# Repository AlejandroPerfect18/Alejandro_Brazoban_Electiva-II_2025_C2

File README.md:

Alejandro_Brazoban_Electiva-II_2025_C2

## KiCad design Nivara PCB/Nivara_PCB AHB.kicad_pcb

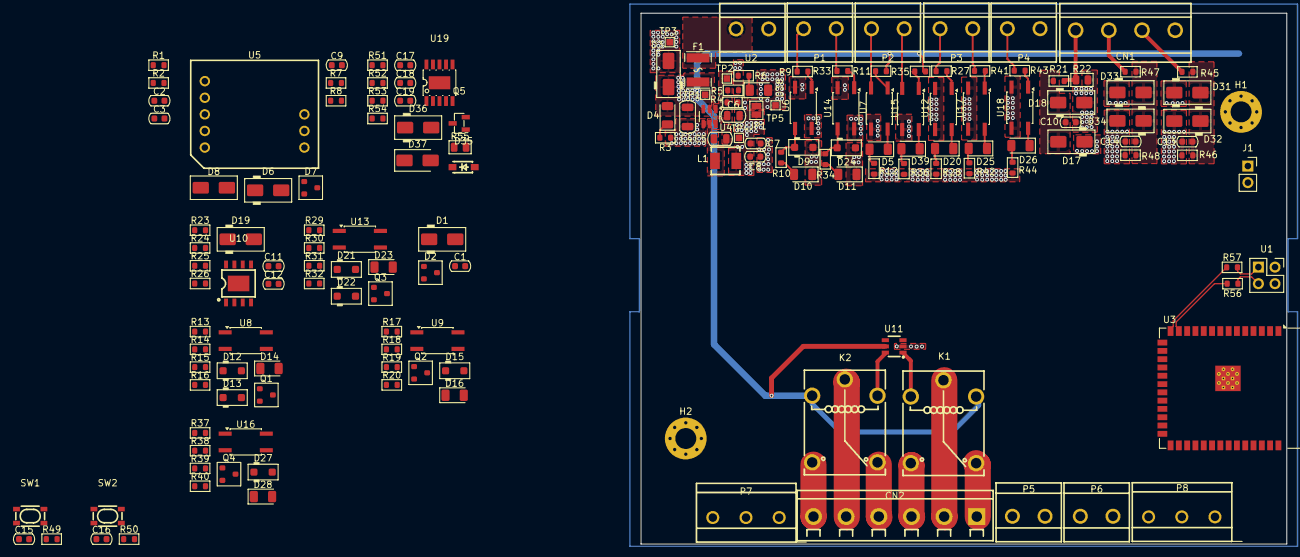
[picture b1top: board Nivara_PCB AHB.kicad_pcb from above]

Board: 4 copper layers, 162 parts (0 on the bottom side), 108 nets.

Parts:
C1, C3, C13, C14: 100nF; C_0603_1608Metric
C2, C7, C8: 22uF; C_0603_1608Metric
C4: 10uF; C_1206_3216Metric
C5: 100nF; C_0805_2012Metric
C6: 100pF; C_0805_2012Metric
C9: 10uF; C_0603_1608Metric
C10: 10nF; C_0603_1608Metric
C11, C19: 0.1uF; C_0603_1608Metric
C12, C15, C16, C18: 1uF; C_0603_1608Metric
C17: 220pF; C_0603_1608Metric
CN1: ANALOG_IN; CONN-TH_DB128V-5.0-4P
CN2: RELAY; CONN-TH_DB126V-5.0-6P-GN
D1: SS12; D_SMA
D2, D7: SM712; SOT-23
D3, D36: SMAJ33A; D_SMA
D4, D5, D10, D11, D14, D16, D20, D23, D25, D26, D28, D38, D39: IR26-21C_L110_TR8; LED_1206_3216Metric
D6, D17, D18, D31, D32, D33, D34: SMAJ5.0A; D_SMA
D8: SMAJ12CA; D_SMA_TVS
D9, D12, D13, D15, D21, D22, D24, D27: PMEG4010CEH; D_SOD-123F
D19: SMAJ12A; D_SMA
D35: BZT52C12_C2891780; SOD-123_L2.7-W1.6-LS3.7-RD-1
D37: MRA4007T3G; D_SMA
F1: BSMD1812-150-33V; F1812
H1, H2: MountingHole_Pad; MountingHole_3.2mm_M3_Pad_Via
J1: AUXILIAR; PinSocket_1x02_P2.54mm_Vertical
JP1: SolderJumper_2_Open; SolderJumper-2_P1.3mm_Open_Pad1.0x1.5mm
K1, K2: SRA-24VDC-CL; RELAY-TH_SRA-X-CX
L1: CXP0420-6R8M-AG(6.8UH); IND-SMD_L4.4-W4.2_CXP0420
P1: NPN_IN; CONN-TH_XY126V-5.0-2P
P2: PNP_IN; CONN-TH_XY126V-5.0-2P
P3: D_IN; CONN-TH_XY126V-5.0-2P
P4: RUN/STOP; CONN-TH_XY126V-5.0-2P
P5: NPN_OUT; CONN-TH_XY126V-5.0-2P
P6: PNP_OUT; CONN-TH_XY126V-5.0-2P
P7: RS485; CONN-TH_3P-P5.00_WJ500V-5.08-3P
P8: ANALOG_OUT.; CONN-TH_3P-P5.00_WJ500V-5.08-3P
Q1, Q3: IRLML0040; SOT-23
Q2, Q4: AO3407A; SOT-23
Q5: IRLML6402TRPBF-JSM; SOT-23-3_L2.9-W1.3-P1.90-LS2.4-BR
R1, R2, R56, R57: 33; R_0603_1608Metric
R3: 1k2; R_0603_1608Metric
R4: 196k; R_0603_1608Metric
R5: 62k; R_0603_1608Metric
R6, R13, R17, R18, R29, R37, R38: 100; R_0603_1608Metric
R7, R8: R_0603; R_0603_1608Metric
R9, R11, R21, R27, R33, R35, R41, R43: 1k; R_0603_1608Metric
R10, R12, R28, R34, R36, R42, R44: 140; R_0603_1608Metric
R14, R30: 22k; R_0603_1608Metric
R15, R31: 20k; R_0603_1608Metric
R16, R20, R32, R40: 1.5k; R_0603_1608Metric
R19, R39, R45, R54: 100k; R_0603_1608Metric
R22: 145; R_0805_2012Metric
R23, R24, R51, R52: 4K7; R_0603_1608Metric
R25: 0; R_0603_1608Metric
R26: 10K; R_0603_1608Metric
R46, R48, R49, R50: 10k; R_0603_1608Metric
R47: 24k; R_0603_1608Metric
R53: 2.5k; R_0603_1608Metric
R55: 15; R_0805_2012Metric
SW1, SW2: SKRPACE010; KEY-SMD_4P-L4.2-W3.2-P2.20-LS4.6
TP1: +VCC1; TestPoint_Pad_1.0x1.0mm
TP2: FB; TestPoint_Pad_1.0x1.0mm
TP3: GND; TestPoint_Pad_1.0x1.0mm
TP4: +3.3V; TestPoint_Pad_1.0x1.0mm
TP5: +3.3Vout; TestPoint_Pad_1.0x1.0mm
U1: 2.54-2*2; PinSocket_2x02_P2.54mm_Vertical
U2: FUENTE IN; CONN-TH_XY126V-5.0-2P
U3: ESP32-S3-WROOM-1
U4: AP63200WU; TSOT-23-6
U5: RSM3485ECHT_C2992406; COMM-TH_8P-L19.5-W16.5-P2.54-BL
U6, U7, U8, U9, U12, U13, U14, U15, U16, U17, U18: LTV-357T; SO-4_4.4x3.6mm_P2.54mm
U10: GP8201S-TC50-EW; ESOP-8_L4.9-W3.9-P1.27-LS6.0-BL-EP
U11: LK1802; SOT-23-6_L2.9-W1.6-P0.95-LS2.8-BR
U19: GP8303-TC50-EW; ESOP-10_L4.9-W3.9-P1.00-LS6.1-BL-EP

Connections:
+3.3V: C2.1, C3.1, C9.1, C15.2, C16.2, D6.1 (K), D17.1 (K), D31.1 (K), D33.1 (K), D38.2 (A), JP1.2 (B), R12.1, R17.1, R23.1, R24.1, R26.1, R28.1, R36.1, R37.1, R42.1, R44.1, R49.1, R50.1, R51.1, R52.1, TP5.1, U3.2 (3V3), U5.1 (VCC), U6.4, U14.4
/D+: D2.1 (A1), R56.1, U1.4
/D-: D2.2 (A2), R57.1, U1.2
/NIVARA_BOARD/4-20mA_IN/ESP_4-20_IN: C10.1, D17.2 (A), D18.1 (K), R21.1, U3.4 (GPIO4/TOUCH4/ADC1_CH3)
/NIVARA_BOARD/A0_10_IN_1: CN1.2, R47.2
/NIVARA_BOARD/A0_32_IN_1: CN1.3, R45.2
/NIVARA_BOARD/A0_V_OUT_1: C11.1, D19.1 (K), P8.1, U10.6 (VOUT)
/NIVARA_BOARD/A4_20_IN_1: CN1.1, R21.2, R22.1
/NIVARA_BOARD/AUX_1: J1.1, R1.2
/NIVARA_BOARD/AUX_2: J1.2, R2.2
/NIVARA_BOARD/A_0-10_IN/A_V_OUT: C14.1, D33.2 (A), D34.1 (K), R47.1, R48.2, U3.6 (GPIO6/TOUCH6/ADC1_CH5)
/NIVARA_BOARD/A_0-32_IN/A_V_OUT: C13.1, D31.2 (A), D32.1 (K), R45.1, R46.2, U3.5 (GPIO5/TOUCH5/ADC1_CH4)
/NIVARA_BOARD/A_I_OUT/SCLK_C: R52.2, U3.21 (GPIO13/TOUCH13/ADC2_CH2/FSPIQ/FSPIIO7/S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), U19.1 (SLCK)
/NIVARA_BOARD/A_I_OUT/SDA_C: R51.2, U3.22 (GPIO14/TOUCH14/ADC2_CH3/FSPIWP/FSPIDQS/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), U19.2 (SDA)
/NIVARA_BOARD/A_V_OUT/ESP_SEL_VOUT: C12.1, R25.2, R26.2, U3.18 (GPIO10/TOUCH10/ADC1_CH9/FSPICS0/FSPIIO4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)
/NIVARA_BOARD/A_V_OUT/SCLK_V: R24.2, U3.19 (GPIO11/TOUCH11/ADC2_CH0/FSPID/FSPIIO5/S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), U10.1 (SCLK)
/NIVARA_BOARD/A_V_OUT/SDA_V: R23.2, U3.20 (GPIO12/TOUCH12/ADC2_CH1/FSPICLK/FSPIIO6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), U10.2 (SDA)
/NIVARA_BOARD/BUTTON1/BUTTON_PIN: R50.2, SW2.3, U3.3 (EN)
/NIVARA_BOARD/BUTTON/BUTTON_PIN: R49.2, SW1.3, U3.27 (GPIO0/BOOT)
/NIVARA_BOARD/DRIVER_RS485/UART_IN: U3.11 (GPIO18/U1RXD/ADC2_CH7/CLK_OUT3), U5.4 (RXD)
/NIVARA_BOARD/DRIVER_RS485/UART_OUT: U3.10 (GPIO17/U1TXD/ADC2_CH6), U5.3 (TXD)
/NIVARA_BOARD/D_IN_1: P3.1, R27.1
/NIVARA_BOARD/D_IN_1/D_OUT: D20.1 (K), U3.28 (SPIIO6/GPIO35/FSPID/SUBSPID), U12.4
/NIVARA_BOARD/D_IN_2: P3.2, R41.1
/NIVARA_BOARD/D_IN_2/D_OUT: D25.1 (K), U3.29 (SPIIO7/GPIO36/FSPICLK/SUBSPICLK), U17.4
/NIVARA_BOARD/I_OUT: D37.1 (K), P8.2
/NIVARA_BOARD/NPN_IN_1: P1.1, R9.1
/NIVARA_BOARD/NPN_IN_1/NPN_OUT: D9.1 (K), R10.1, U3.32 (MTCK/GPIO39/CLK_OUT3/SUBSPICS1), U6.3
/NIVARA_BOARD/NPN_IN_2: P1.2, R33.1
/NIVARA_BOARD/NPN_IN_2/NPN_OUT: D24.1 (K), R34.1, U3.33 (MTDO/GPIO40/CLK_OUT2), U14.3
/NIVARA_BOARD/NPN_OUT_1: P5.1, R13.1
/NIVARA_BOARD/NPN_OUT_1/NPN_OUT: D13.2 (A), D14.1 (K), Q1.3 (D), U3.34 (MTDI/GPIO41/CLK_OUT1)
/NIVARA_BOARD/NPN_OUT_2: P5.2, R29.1
/NIVARA_BOARD/NPN_OUT_2/NPN_OUT: D22.2 (A), D23.1 (K), Q3.3 (D), U3.35 (MTMS/GPIO42)
/NIVARA_BOARD/PNP_IN_1: P2.1, U7.2
/NIVARA_BOARD/PNP_IN_1/PNP_OUT: D5.1 (K), U3.8 (GPIO15/U0RTS/ADC2_CH4/XTAL_32K_P), U7.4
/NIVARA_BOARD/PNP_IN_2: P2.2, U15.2
/NIVARA_BOARD/PNP_IN_2/PNP_OUT: D39.1 (K), U3.9 (GPIO16/U0CTS/ADC2_CH5/XTAL_32K_N), U15.4
/NIVARA_BOARD/PNP_OUT_1: D15.1 (K), P6.1, Q2.3 (D), R20.1
/NIVARA_BOARD/PNP_OUT_1/PNP_IN: U3.23 (GPIO21), U9.2
/NIVARA_BOARD/PNP_OUT_2: D27.1 (K), P6.2, Q4.3 (D), R40.1
/NIVARA_BOARD/PNP_OUT_2/PNP_IN: U3.24 (GPIO47/SPICLK_P/SUBSPICLK_P_DIFF), U16.2
/NIVARA_BOARD/PowerSupply/BST: C5.1, U4.6 (BST)
/NIVARA_BOARD/PowerSupply/FB: C6.1, R4.2, R5.1, TP2.1, U4.1 (FB)
/NIVARA_BOARD/PowerSupply/SW: C5.2, L1.1, U4.5 (SW)
/NIVARA_BOARD/PowerSupply/VOUT: C6.2, C7.1, C8.1, JP1.1 (A), L1.2, R4.1, TP4.1
/NIVARA_BOARD/RELAY1&2/ESP_RLY2: U3.39 (GPIO1/TOUCH1/ADC1_CH0), U11.3 (1B)
/NIVARA_BOARD/RELAY1&2/ESP_RY1: U3.38 (GPIO2/TOUCH2/ADC1_CH1), U11.4 (2B)
/NIVARA_BOARD/RLY_1_C: CN2.2, K1.5
/NIVARA_BOARD/RLY_1_NC: CN2.1, K1.2
/NIVARA_BOARD/RLY_1_NO: CN2.3, K1.1
/NIVARA_BOARD/RLY_2_C: CN2.5, K2.5
/NIVARA_BOARD/RLY_2_NC: CN2.4, K2.2
/NIVARA_BOARD/RLY_2_NO: CN2.6, K2.1
/NIVARA_BOARD/RS485_A: P7.1, R7.2
/NIVARA_BOARD/RS485_B: P7.2, R8.2
/NIVARA_BOARD/RUN_STOP/D_OUT: D26.1 (K), U3.30 (SPIDQS/GPIO37/FSPIQ/SUBSPIQ), U18.4
/NIVARA_BOARD/RUN/STOP: P4.1, R43.1
/NIVARA_BOARD/USB_D+: R56.2, U3.13 (GPIO19/U1RTS/ADC2_CH8/CLK_OUT2/USB_D-)
/NIVARA_BOARD/USB_D-: R57.2, U3.14 (GPIO20/U1CTS/ADC2_CH9/CLK_OUT1/USB_D+)
/VIN: F1.1, U2.1
GND: C1.2, C2.2, C3.2, C4.2, C7.2, C8.2, C9.2, C10.2, C11.2, C12.2, C13.2, C14.2, C15.1, C16.1, C17.2, C18.2, C19.2, CN1.4, D2.3 (Com), D3.2 (A), D6.2 (A), D7.3 (Com), D9.2 (A), D10.1 (K), D11.1 (K), D12.2 (A), D15.2 (A), D16.1 (K), D18.2 (A), D19.2 (A), D21.2 (A), D24.2 (A), D27.2 (A), D28.1 (K), D32.2 (A), D34.2 (A), D36.2 (A), H1.1, H2.1, P4.2, P7.3, P8.3, Q1.2 (S), Q3.2 (S), R3.1, R5.2, R6.1, R14.2, R22.2, R30.2, R46.1, R48.1, R53.2, R54.2, SW1.2, SW2.2, TP3.1, U1.1, U2.2, U3.1 (GND), U3.40 (GND), U3.41 (GND), U4.4 (GND), U5.2 (GND), U5.5 (CON), U6.2, U7.3, U8.2, U9.3, U10.5 (GND), U11.2 (E), U12.2, U12.3, U13.2, U14.2, U15.3, U16.3, U17.2, U17.3, U18.2, U18.3, U19.6 (GND)
unnamed: D1.2 (A), U1.3
unnamed: D4.1 (K), R3.2
unnamed: D5.2 (A), R12.2
unnamed: D7.1 (A1), D8.2 (A), R7.1, U5.9 (A)
unnamed: D7.2 (A2), D8.1 (K), R8.1, U5.8 (B)
unnamed: D10.2 (A), R10.2
unnamed: D11.2 (A), R34.2
unnamed: D12.1 (K), Q1.1 (G), R14.1, U8.3
unnamed: D14.2 (A), R16.2
unnamed: D16.2 (A), R20.2
unnamed: D20.2 (A), R28.2
unnamed: D21.1 (K), Q3.1 (G), R30.1, U13.3
unnamed: D23.2 (A), R32.2
unnamed: D25.2 (A), R42.2
unnamed: D26.2 (A), R44.2
unnamed: D28.2 (A), R40.2
unnamed: C18.1, D35.2 (A), Q5.1 (G), R54.1
unnamed: C19.1, D36.1 (K), Q5.3 (D), R55.1
unnamed: D37.2 (A), R55.2
unnamed: D38.1 (K), R6.2
unnamed: D39.2 (A), R36.2
unnamed: Q2.1 (G), R18.1, R19.2
unnamed: Q4.1 (G), R38.1, R39.2
unnamed: Q5.2 (S), U19.8 (IOUT)
unnamed: R9.2, U6.1
unnamed: R11.2, U7.1
unnamed: R13.2, U8.1
unnamed: R15.2, U8.4
unnamed: R17.2, U9.1
unnamed: R18.2, U9.4
unnamed: R27.2, U12.1
unnamed: R29.2, U13.1
unnamed: R31.2, U13.4
unnamed: R33.2, U14.1
unnamed: R35.2, U15.1
unnamed: R37.2, U16.1
unnamed: R38.2, U16.4
unnamed: R41.2, U17.1
unnamed: R43.2, U18.1
unnamed: R2.1, U3.26 (GPIO45)
unnamed: R1.1, U3.25 (GPIO48/SPICLK_N/SUBSPICLK_N_DIFF)
unnamed: R25.1, U10.7 (SEL)
unnamed: K1.4, U11.1 (1C)
unnamed: K2.3, U11.6 (2C)
unnamed: C17.1, R53.1, U19.7 (SET)
VCC: C1.1, C4.1, D1.1 (K), D3.1 (K), D4.2 (A), D13.1 (K), D22.1 (K), D35.1 (K), F1.2, K1.3, K2.4, Q2.2 (S), Q4.2 (S), R11.1, R15.1, R16.1, R19.1, R31.1, R32.1, R35.1, R39.1, TP1.1, U4.2 (EN), U4.3 (IN), U10.4 (VCC), U11.5 (COM), U19.5 (VCC)

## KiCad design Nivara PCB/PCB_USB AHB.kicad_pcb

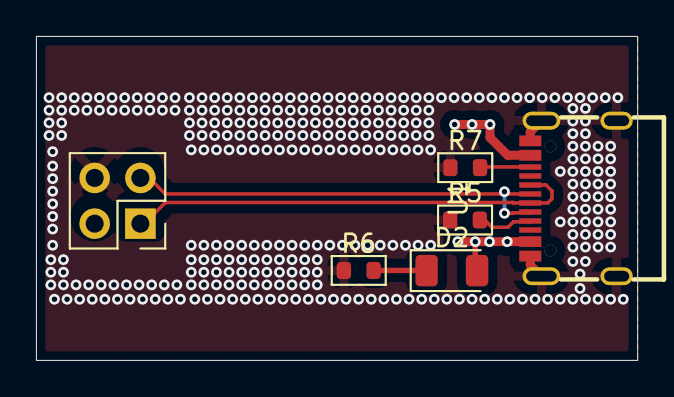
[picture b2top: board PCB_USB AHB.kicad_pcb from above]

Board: 2 copper layers, 33.4 x 18.0 mm, 6 parts (0 on the bottom side), 7 nets.

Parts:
D2: IR26-21C_L110_TR8; LED_1206_3216Metric
J1: PINHD_2x2_Male; PinHeader_2x02_P2.54mm_Vertical
R5, R7: 5.1K; R_0603_1608Metric
R6: 500; R_0603_1608Metric
U1: GT-USB-7010ASV; USB-C-SMD_G-SWITCH_GT-USB-7010ASV

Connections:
+5V: D2.2 (A), J1.2, U1.A4B9 (VBUS), U1.B4A9 (VBUS)
/D+: J1.1, U1.A6 (DP1), U1.B6 (DP2)
/D-: J1.3, U1.A7 (DN1), U1.B7 (DN2)
GND: J1.4, R5.1, R6.1, R7.1, U1.1 (SHELL), U1.2 (SHELL), U1.3 (SHELL), U1.4 (SHELL), U1.A1B12 (GND), U1.B1A12 (GND)
unnamed: D2.1 (K), R6.2
unnamed: R5.2, U1.A5 (CC1)
unnamed: R7.2, U1.B5 (CC2)

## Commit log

2025-07-16 Alejandro_Brazoban_Electiva-II_2025_C2
